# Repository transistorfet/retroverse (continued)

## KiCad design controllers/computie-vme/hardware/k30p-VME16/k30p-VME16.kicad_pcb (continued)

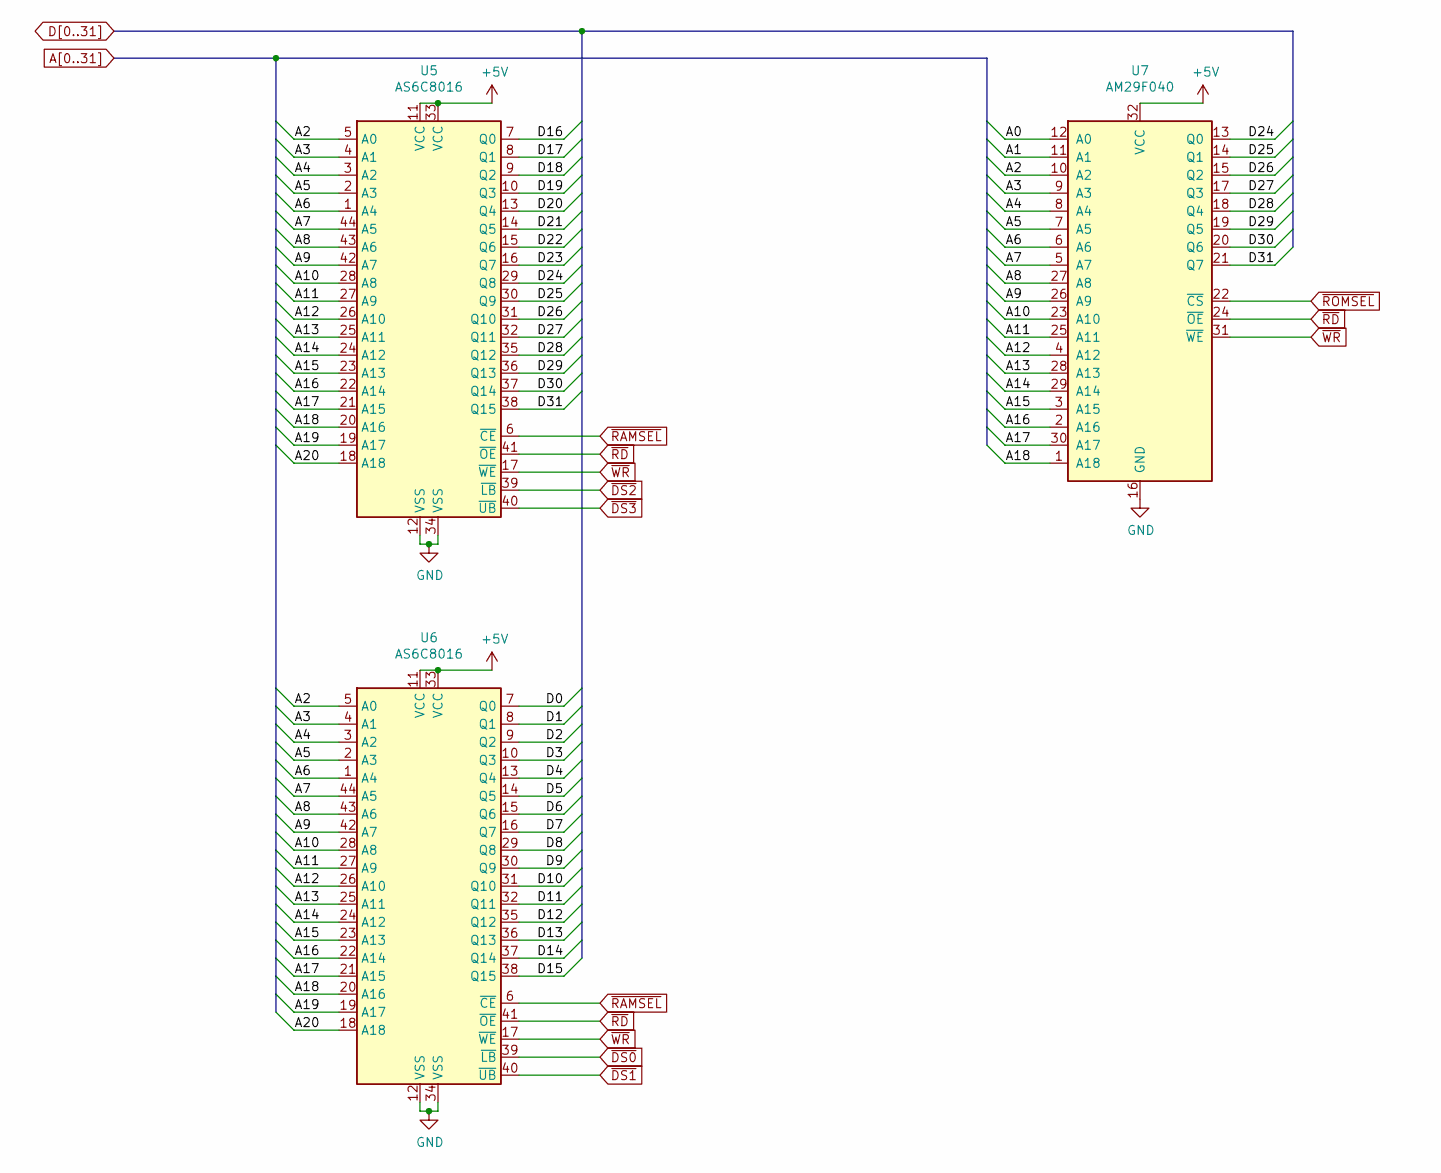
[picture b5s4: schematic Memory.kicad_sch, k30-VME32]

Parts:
U5, U6: AS6C8016; TSOP-II-44_10.16x18.41mm_P0.8mm
U7: AM29F040; PLCC-32_THT-Socket

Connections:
+5V: U5.11 (VCC), U5.33 (VCC), U6.11 (VCC), U6.33 (VCC), U7.32 (VCC); also elsewhere on the board
A0: U7.12 (A0)
A1: U7.11 (A1); also elsewhere on the board
A2: U5.5 (A0), U6.5 (A0), U7.10 (A2); also elsewhere on the board
A3: U5.4 (A1), U6.4 (A1), U7.9 (A3); also elsewhere on the board
A4: U5.3 (A2), U6.3 (A2), U7.8 (A4); also elsewhere on the board
A5: U5.2 (A3), U6.2 (A3), U7.7 (A5)
A6: U5.1 (A4), U6.1 (A4), U7.6 (A6)
A7: U5.44 (A5), U6.44 (A5), U7.5 (A7)
A8: U5.43 (A6), U6.43 (A6), U7.27 (A8)
A9: U5.42 (A7), U6.42 (A7), U7.26 (A9)
A10: U5.28 (A8), U6.28 (A8), U7.23 (A10)
A11: U5.27 (A9), U6.27 (A9), U7.25 (A11)
A12: U5.26 (A10), U6.26 (A10), U7.4 (A12)
A13: U5.25 (A11), U6.25 (A11), U7.28 (A13)
A14: U5.24 (A12), U6.24 (A12), U7.29 (A14)
A15: U5.23 (A13), U6.23 (A13), U7.3 (A15)
A16: U5.22 (A14), U6.22 (A14), U7.2 (A16)
A17: U5.21 (A15), U6.21 (A15), U7.30 (A17)
A18: U5.20 (A16), U6.20 (A16), U7.1 (A18)
A19: U5.19 (A17), U6.19 (A17)
A20: U5.18 (A18), U6.18 (A18)
D0: U6.7 (Q0)
D1: U6.8 (Q1)
D2: U6.9 (Q2)
D3: U6.10 (Q3)
D4: U6.13 (Q4)
D5: U6.14 (Q5)
D6: U6.15 (Q6)
D7: U6.16 (Q7)
D8: U6.29 (Q8)
D9: U6.30 (Q9)
D10: U6.31 (Q10)
D11: U6.32 (Q11)
D12: U6.35 (Q12)
D13: U6.36 (Q13)
D14: U6.37 (Q14)
D15: U6.38 (Q15)
D16: U5.7 (Q0)
D17: U5.8 (Q1)
D18: U5.9 (Q2)
D19: U5.10 (Q3)
D20: U5.13 (Q4)
D21: U5.14 (Q5)
D22: U5.15 (Q6)
D23: U5.16 (Q7)
D24: U5.29 (Q8), U7.13 (Q0); also elsewhere on the board
D25: U5.30 (Q9), U7.14 (Q1); also elsewhere on the board
D26: U5.31 (Q10), U7.15 (Q2); also elsewhere on the board
D27: U5.32 (Q11), U7.17 (Q3); also elsewhere on the board
D28: U5.35 (Q12), U7.18 (Q4); also elsewhere on the board
D29: U5.36 (Q13), U7.19 (Q5); also elsewhere on the board
D30: U5.37 (Q14), U7.20 (Q6); also elsewhere on the board
D31: U5.38 (Q15), U7.21 (Q7); also elsewhere on the board
GND: U5.12 (VSS), U5.34 (VSS), U6.12 (VSS), U6.34 (VSS), U7.16 (GND); also elsewhere on the board
~DS0: U6.39 (~LB)
~DS1: U6.40 (~UB)
~DS2: U5.39 (~LB)
~DS3: U5.40 (~UB)
~RAMSEL: U5.6 (~CE), U6.6 (~CE)
~RD: U5.41 (~OE), U6.41 (~OE), U7.24 (~OE); also elsewhere on the board
~ROMSEL: U7.22 (~CS)
~WR: U5.17 (~WE), U6.17 (~WE), U7.31 (~WE); also elsewhere on the board

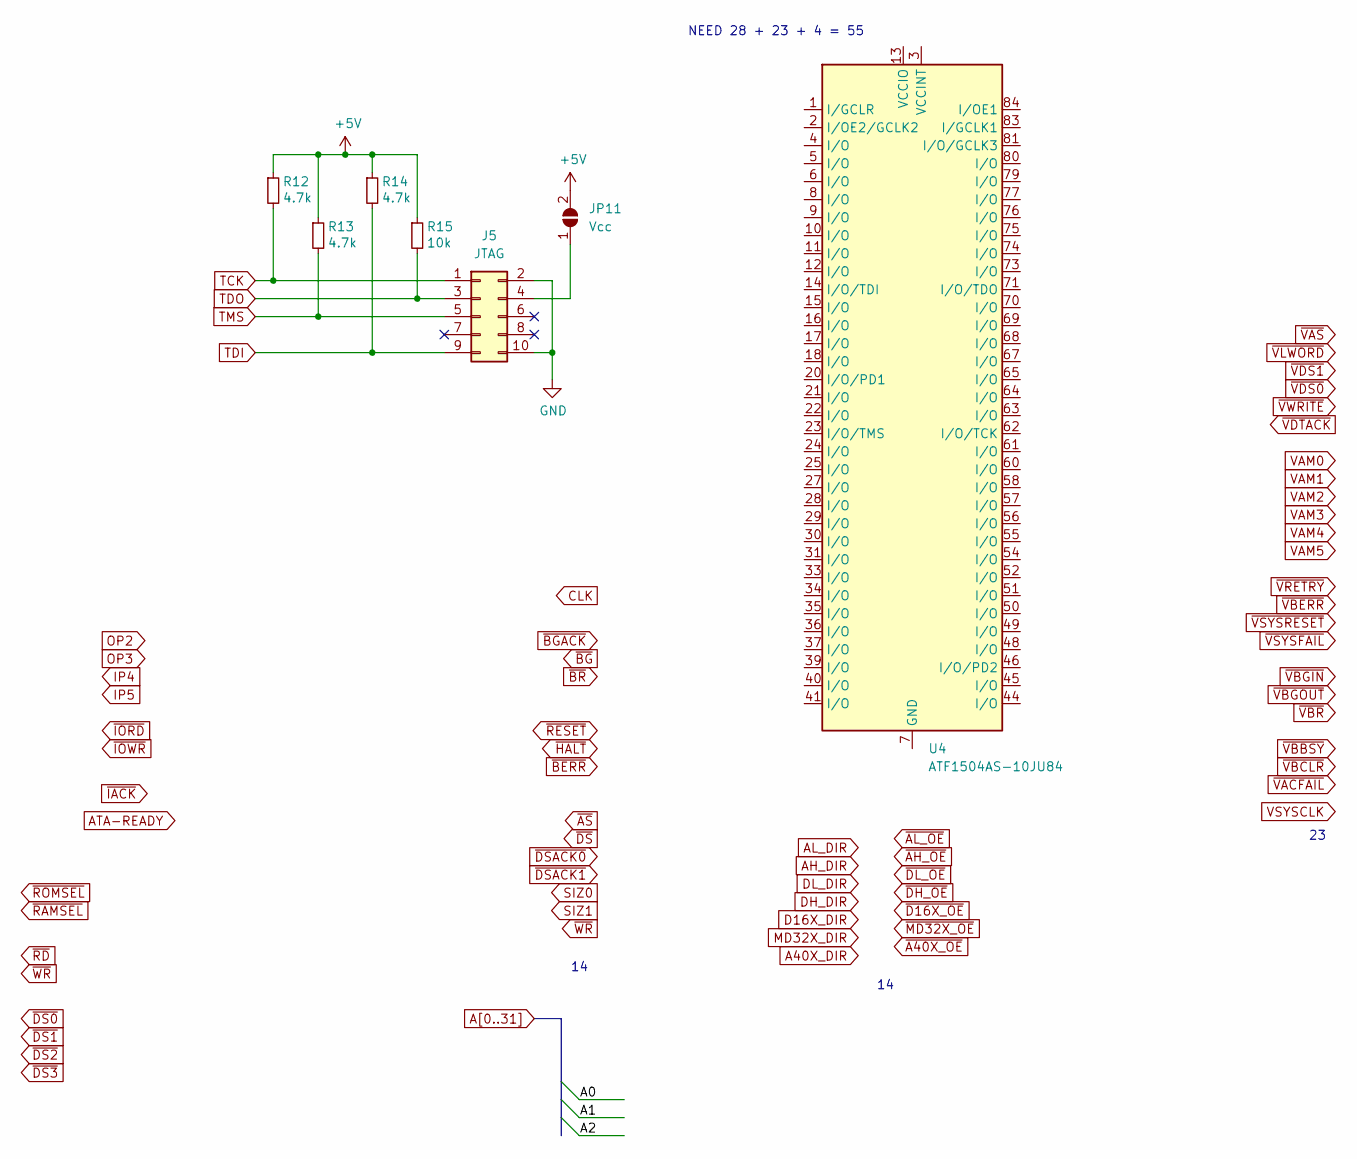
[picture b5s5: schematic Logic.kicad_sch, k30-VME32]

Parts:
J5: JTAG; PinHeader_2x05_P2.54mm_Vertical
JP11: Vcc; SolderJumper-2_P1.3mm_Open_RoundedPad1.0x1.5mm
R12, R13, R14: 4.7k; R_Axial_DIN0204_L3.6mm_D1.6mm_P5.08mm_Horizontal
R15: 10k; R_Axial_DIN0204_L3.6mm_D1.6mm_P5.08mm_Horizontal
U4: ATF1504AS-10JU84; PLCC-84_THT-Socket

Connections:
+5V: JP11.2 (B), R12.1, R13.1, R14.1, R15.1; also elsewhere on the board
GND: J5.2, J5.10; also elsewhere on the board
unnamed: J5.4, JP11.1 (A)
unnamed: U4.7 (GND), U4.19 (GND), U4.32 (GND), U4.42 (GND), U4.47 (GND), U4.59 (GND), U4.72 (GND), U4.82 (GND)
unnamed: U4.3 (VCCINT), U4.43 (VCCINT)
unnamed: U4.13 (VCCIO), U4.26 (VCCIO), U4.38 (VCCIO), U4.53 (VCCIO), U4.66 (VCCIO), U4.78 (VCCIO)
TCK: J5.1, R12.2
TDI: J5.9, R14.2
TDO: J5.3, R15.2
TMS: J5.5, R13.2

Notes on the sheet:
NEED 28 + 23 + 4 = 55

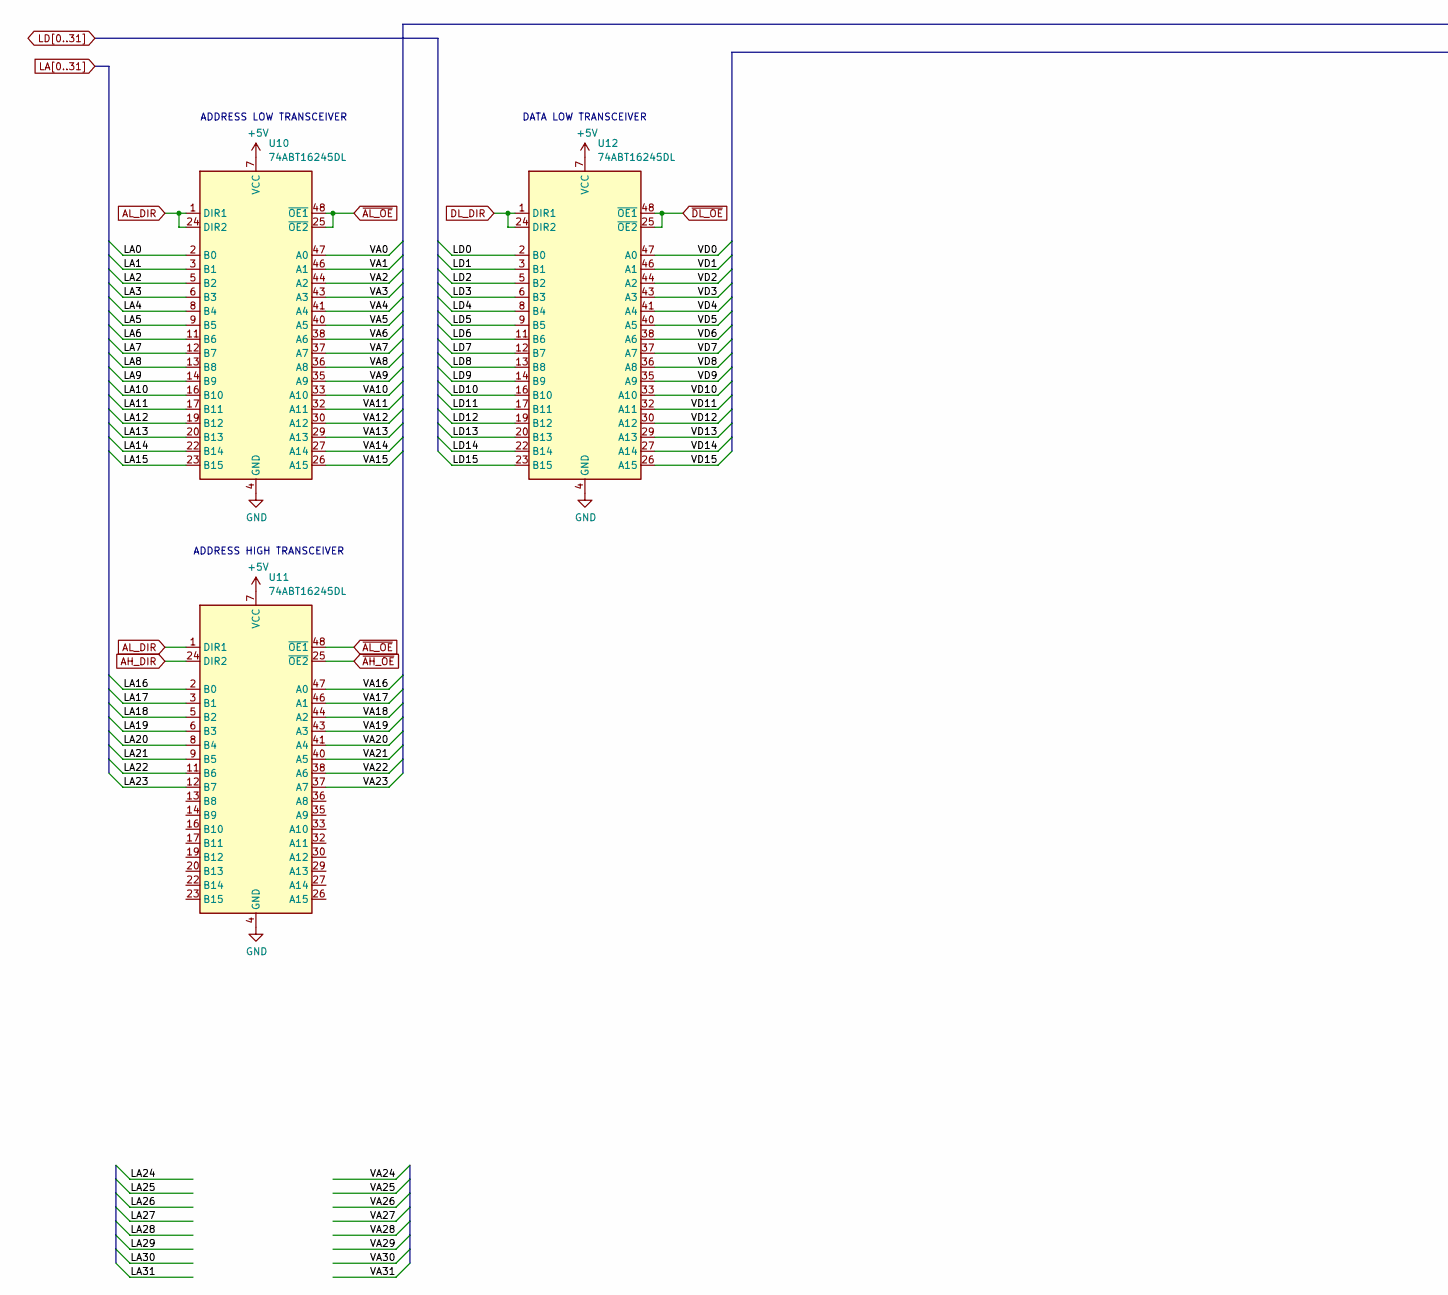
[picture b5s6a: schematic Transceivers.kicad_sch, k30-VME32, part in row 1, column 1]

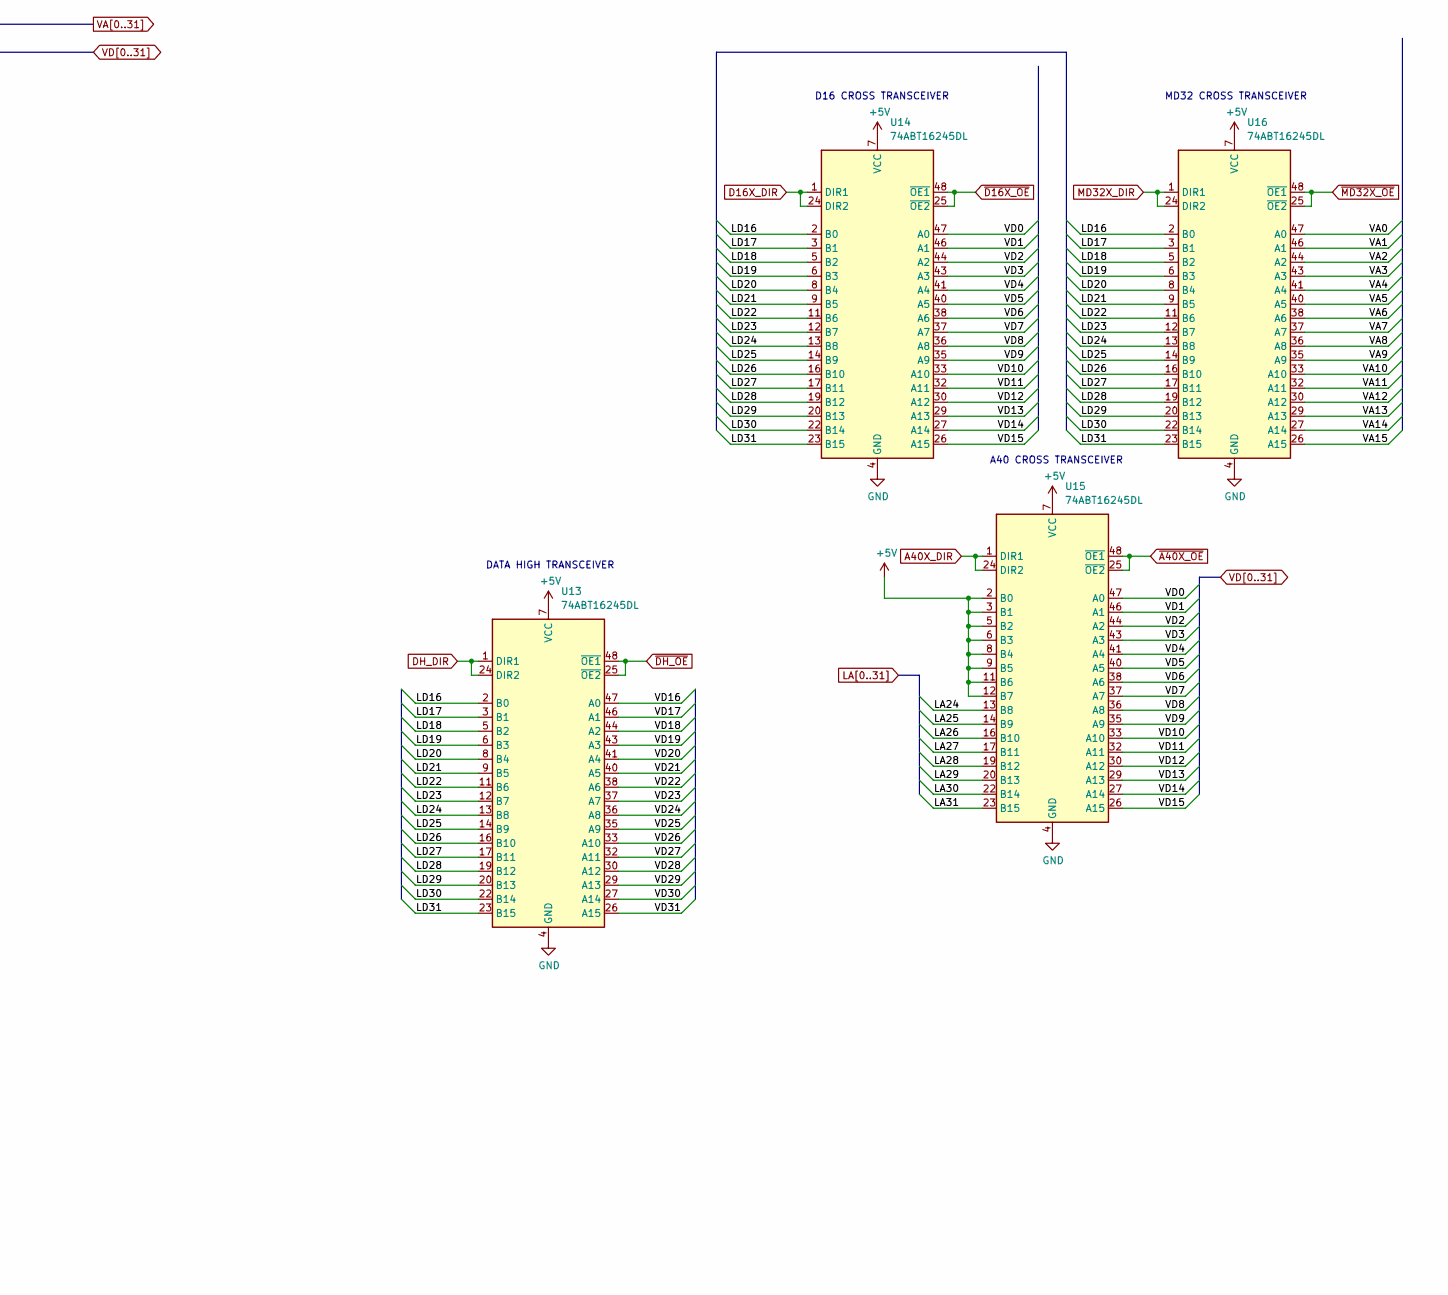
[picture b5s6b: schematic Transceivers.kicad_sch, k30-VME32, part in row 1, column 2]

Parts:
U10, U11, U12, U13, U14, U15, U16: 74ABT16245DL; TSSOP-48_6.1x12.5mm_P0.5mm

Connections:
+5V: U10.7 (VCC), U10.18 (VCC), U10.31 (VCC), U10.42 (VCC), U11.7 (VCC), U11.18 (VCC), U11.31 (VCC), U11.42 (VCC), U12.7 (VCC), U12.18 (VCC), U12.31 (VCC), U12.42 (VCC), U13.7 (VCC), U13.18 (VCC), U13.31 (VCC), U13.42 (VCC), U14.7 (VCC), U14.18 (VCC), U14.31 (VCC), U14.42 (VCC), U15.2 (B0), U15.3 (B1), U15.5 (B2), U15.6 (B3), U15.7 (VCC), U15.8 (B4), U15.9 (B5), U15.11 (B6), U15.12 (B7), U15.18 (VCC), U15.31 (VCC), U15.42 (VCC), U16.7 (VCC), U16.18 (VCC), U16.31 (VCC), U16.42 (VCC); also elsewhere on the board
A40X_DIR: U15.1 (DIR1), U15.24 (DIR2)
AH_DIR: U11.24 (DIR2)
AL_DIR: U10.1 (DIR1), U10.24 (DIR2), U11.1 (DIR1)
D16X_DIR: U14.1 (DIR1), U14.24 (DIR2)
DH_DIR: U13.1 (DIR1), U13.24 (DIR2)
DL_DIR: U12.1 (DIR1), U12.24 (DIR2)
GND: U10.4 (GND), U10.10 (GND), U10.15 (GND), U10.21 (GND), U10.28 (GND), U10.34 (GND), U10.39 (GND), U10.45 (GND), U11.4 (GND), U11.10 (GND), U11.15 (GND), U11.21 (GND), U11.28 (GND), U11.34 (GND), U11.39 (GND), U11.45 (GND), U12.4 (GND), U12.10 (GND), U12.15 (GND), U12.21 (GND), U12.28 (GND), U12.34 (GND), U12.39 (GND), U12.45 (GND), U13.4 (GND), U13.10 (GND), U13.15 (GND), U13.21 (GND), U13.28 (GND), U13.34 (GND), U13.39 (GND), U13.45 (GND), U14.4 (GND), U14.10 (GND), U14.15 (GND), U14.21 (GND), U14.28 (GND), U14.34 (GND), U14.39 (GND), U14.45 (GND), U15.4 (GND), U15.10 (GND), U15.15 (GND), U15.21 (GND), U15.28 (GND), U15.34 (GND), U15.39 (GND), U15.45 (GND), U16.4 (GND), U16.10 (GND), U16.15 (GND), U16.21 (GND), U16.28 (GND), U16.34 (GND), U16.39 (GND), U16.45 (GND); also elsewhere on the board
LA0: U10.2 (B0); also elsewhere on the board
LA1: U10.3 (B1); also elsewhere on the board
LA2: U10.5 (B2); also elsewhere on the board
LA3: U10.6 (B3); also elsewhere on the board
LA4: U10.8 (B4); also elsewhere on the board
LA5: U10.9 (B5); also elsewhere on the board
LA6: U10.11 (B6); also elsewhere on the board
LA7: U10.12 (B7); also elsewhere on the board
LA8: U10.13 (B8); also elsewhere on the board
LA9: U10.14 (B9); also elsewhere on the board
LA10: U10.16 (B10); also elsewhere on the board
LA11: U10.17 (B11); also elsewhere on the board
LA12: U10.19 (B12); also elsewhere on the board
LA13: U10.20 (B13); also elsewhere on the board
LA14: U10.22 (B14); also elsewhere on the board
LA15: U10.23 (B15); also elsewhere on the board
LA16: U11.2 (B0); also elsewhere on the board
LA17: U11.3 (B1); also elsewhere on the board
LA18: U11.5 (B2); also elsewhere on the board
LA19: U11.6 (B3); also elsewhere on the board
LA20: U11.8 (B4); also elsewhere on the board
LA21: U11.9 (B5); also elsewhere on the board
LA22: U11.11 (B6); also elsewhere on the board
LA23: U11.12 (B7); also elsewhere on the board
LA24: U15.13 (B8); also elsewhere on the board
LA25: U15.14 (B9); also elsewhere on the board
LA26: U15.16 (B10); also elsewhere on the board
LA27: U15.17 (B11); also elsewhere on the board
LA28: U15.19 (B12); also elsewhere on the board
LA29: U15.20 (B13); also elsewhere on the board
LA30: U15.22 (B14); also elsewhere on the board
LA31: U15.23 (B15); also elsewhere on the board
LD0: U12.2 (B0); also elsewhere on the board
LD1: U12.3 (B1); also elsewhere on the board
LD2: U12.5 (B2); also elsewhere on the board
LD3: U12.6 (B3); also elsewhere on the board
LD4: U12.8 (B4); also elsewhere on the board
LD5: U12.9 (B5); also elsewhere on the board
LD6: U12.11 (B6); also elsewhere on the board
LD7: U12.12 (B7); also elsewhere on the board
LD8: U12.13 (B8); also elsewhere on the board
LD9: U12.14 (B9); also elsewhere on the board
LD10: U12.16 (B10); also elsewhere on the board
LD11: U12.17 (B11); also elsewhere on the board
LD12: U12.19 (B12); also elsewhere on the board
LD13: U12.20 (B13); also elsewhere on the board
LD14: U12.22 (B14); also elsewhere on the board
LD15: U12.23 (B15); also elsewhere on the board
LD16: U13.2 (B0), U14.2 (B0), U16.2 (B0); also elsewhere on the board
LD17: U13.3 (B1), U14.3 (B1), U16.3 (B1); also elsewhere on the board
LD18: U13.5 (B2), U14.5 (B2), U16.5 (B2); also elsewhere on the board
LD19: U13.6 (B3), U14.6 (B3), U16.6 (B3); also elsewhere on the board
LD20: U13.8 (B4), U14.8 (B4), U16.8 (B4); also elsewhere on the board
LD21: U13.9 (B5), U14.9 (B5), U16.9 (B5); also elsewhere on the board
LD22: U13.11 (B6), U14.11 (B6), U16.11 (B6); also elsewhere on the board
LD23: U13.12 (B7), U14.12 (B7), U16.12 (B7); also elsewhere on the board
LD24: U13.13 (B8), U14.13 (B8), U16.13 (B8); also elsewhere on the board
LD25: U13.14 (B9), U14.14 (B9), U16.14 (B9); also elsewhere on the board
LD26: U13.16 (B10), U14.16 (B10), U16.16 (B10); also elsewhere on the board
LD27: U13.17 (B11), U14.17 (B11), U16.17 (B11); also elsewhere on the board
LD28: U13.19 (B12), U14.19 (B12), U16.19 (B12); also elsewhere on the board
LD29: U13.20 (B13), U14.20 (B13), U16.20 (B13); also elsewhere on the board
LD30: U13.22 (B14), U14.22 (B14), U16.22 (B14); also elsewhere on the board
LD31: U13.23 (B15), U14.23 (B15), U16.23 (B15); also elsewhere on the board
MD32X_DIR: U16.1 (DIR1), U16.24 (DIR2)
VA0: U10.47 (A0), U16.47 (A0)
VA1: U10.46 (A1), U16.46 (A1); also elsewhere on the board
VA2: U10.44 (A2), U16.44 (A2); also elsewhere on the board
VA3: U10.43 (A3), U16.43 (A3); also elsewhere on the board
VA4: U10.41 (A4), U16.41 (A4); also elsewhere on the board
VA5: U10.40 (A5), U16.40 (A5); also elsewhere on the board
VA6: U10.38 (A6), U16.38 (A6); also elsewhere on the board
VA7: U10.37 (A7), U16.37 (A7); also elsewhere on the board
VA8: U10.36 (A8), U16.36 (A8); also elsewhere on the board
VA9: U10.35 (A9), U16.35 (A9); also elsewhere on the board
VA10: U10.33 (A10), U16.33 (A10); also elsewhere on the board
VA11: U10.32 (A11), U16.32 (A11); also elsewhere on the board
VA12: U10.30 (A12), U16.30 (A12); also elsewhere on the board
VA13: U10.29 (A13), U16.29 (A13); also elsewhere on the board
VA14: U10.27 (A14), U16.27 (A14); also elsewhere on the board
VA15: U10.26 (A15), U16.26 (A15); also elsewhere on the board
VA16: U11.47 (A0); also elsewhere on the board
VA17: U11.46 (A1); also elsewhere on the board
VA18: U11.44 (A2); also elsewhere on the board
VA19: U11.43 (A3); also elsewhere on the board
VA20: U11.41 (A4); also elsewhere on the board
VA21: U11.40 (A5); also elsewhere on the board
VA22: U11.38 (A6); also elsewhere on the board
VA23: U11.37 (A7); also elsewhere on the board
VD0: U12.47 (A0), U14.47 (A0), U15.47 (A0); also elsewhere on the board
VD1: U12.46 (A1), U14.46 (A1), U15.46 (A1); also elsewhere on the board
VD2: U12.44 (A2), U14.44 (A2), U15.44 (A2); also elsewhere on the board
VD3: U12.43 (A3), U14.43 (A3), U15.43 (A3); also elsewhere on the board
VD4: U12.41 (A4), U14.41 (A4), U15.41 (A4); also elsewhere on the board
VD5: U12.40 (A5), U14.40 (A5), U15.40 (A5); also elsewhere on the board
VD6: U12.38 (A6), U14.38 (A6), U15.38 (A6); also elsewhere on the board
VD7: U12.37 (A7), U14.37 (A7), U15.37 (A7); also elsewhere on the board
VD8: U12.36 (A8), U14.36 (A8), U15.36 (A8); also elsewhere on the board
VD9: U12.35 (A9), U14.35 (A9), U15.35 (A9); also elsewhere on the board
VD10: U12.33 (A10), U14.33 (A10), U15.33 (A10); also elsewhere on the board
VD11: U12.32 (A11), U14.32 (A11), U15.32 (A11); also elsewhere on the board
VD12: U12.30 (A12), U14.30 (A12), U15.30 (A12); also elsewhere on the board
VD13: U12.29 (A13), U14.29 (A13), U15.29 (A13); also elsewhere on the board
VD14: U12.27 (A14), U14.27 (A14), U15.27 (A14); also elsewhere on the board
VD15: U12.26 (A15), U14.26 (A15), U15.26 (A15); also elsewhere on the board
VD16: U13.47 (A0)
VD17: U13.46 (A1)
VD18: U13.44 (A2)
VD19: U13.43 (A3)
VD20: U13.41 (A4)
VD21: U13.40 (A5)
VD22: U13.38 (A6)
VD23: U13.37 (A7)
VD24: U13.36 (A8)
VD25: U13.35 (A9)
VD26: U13.33 (A10)
VD27: U13.32 (A11)
VD28: U13.30 (A12)
VD29: U13.29 (A13)
VD30: U13.27 (A14)
VD31: U13.26 (A15)
~A40X_OE: U15.25 (~OE2), U15.48 (~OE1)
~AH_OE: U11.25 (~OE2)
~AL_OE: U10.25 (~OE2), U10.48 (~OE1), U11.48 (~OE1)
~D16X_OE: U14.25 (~OE2), U14.48 (~OE1)
~DH_OE: U13.25 (~OE2), U13.48 (~OE1)
~DL_OE: U12.25 (~OE2), U12.48 (~OE1)
~MD32X_OE: U16.25 (~OE2), U16.48 (~OE1)

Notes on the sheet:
D16 CROSS TRANSCEIVER
ADDRESS HIGH TRANSCEIVER
MD32 CROSS TRANSCEIVER
ADDRESS LOW TRANSCEIVER
A40 CROSS TRANSCEIVER
DATA LOW TRANSCEIVER
DATA HIGH TRANSCEIVER

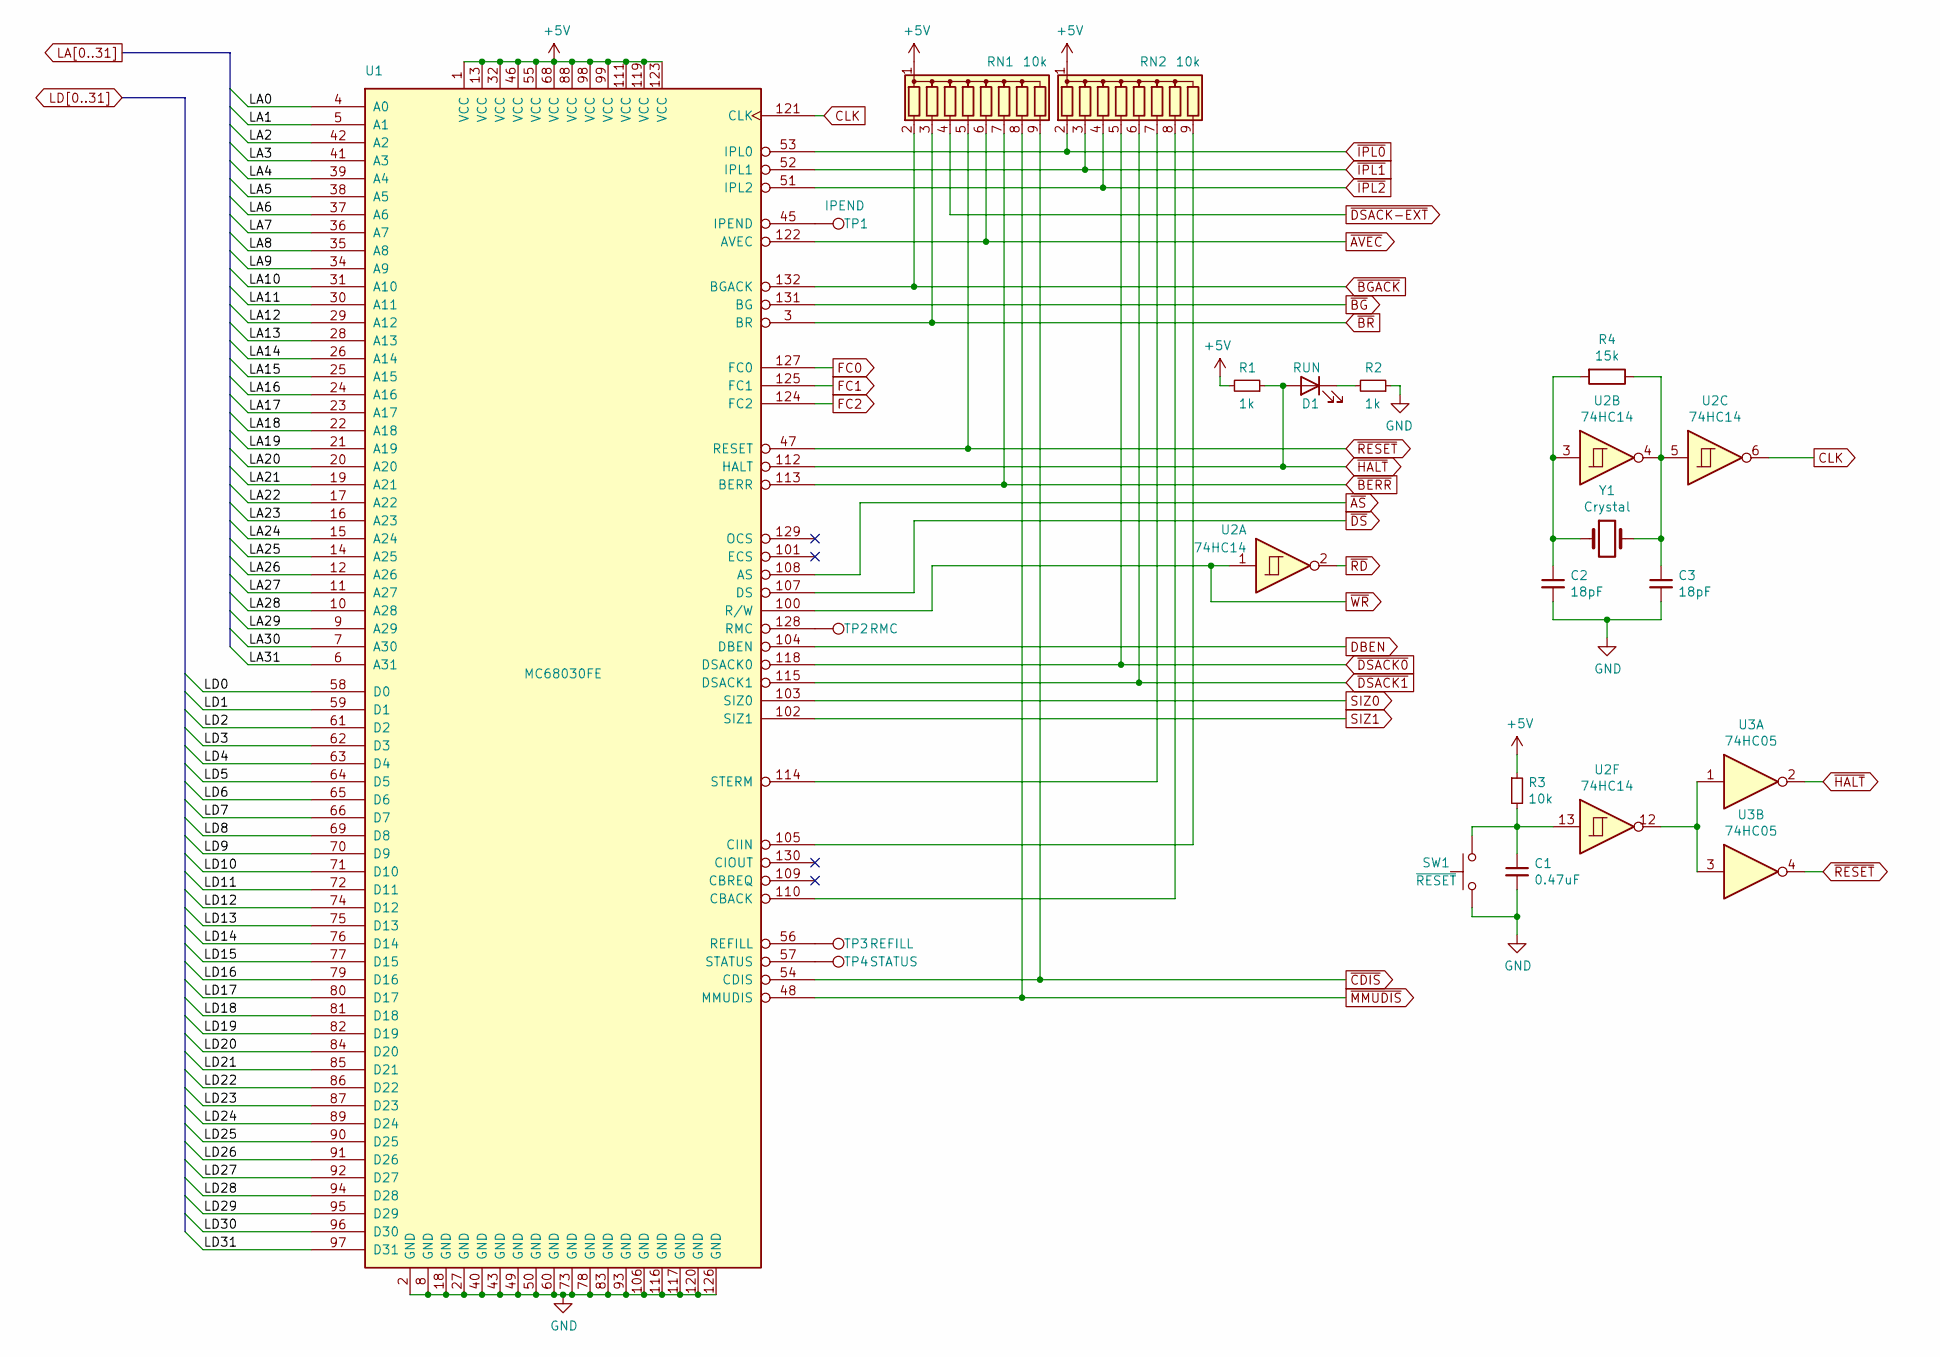
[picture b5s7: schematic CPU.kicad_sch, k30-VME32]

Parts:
C1: 0.47uF; C_Disc_D3.0mm_W2.0mm_P2.50mm
C2, C3: 18pF; C_Disc_D3.0mm_W2.0mm_P2.50mm
D1: RUN; LED_D5.0mm
R1, R2: 1k; R_Axial_DIN0204_L3.6mm_D1.6mm_P5.08mm_Horizontal
R3: 10k; R_Axial_DIN0204_L3.6mm_D1.6mm_P5.08mm_Horizontal
R4: 15k; R_Axial_DIN0204_L3.6mm_D1.6mm_P5.08mm_Horizontal
RN1, RN2: 10k; R_Array_SIP9
SW1: ~{RESET}; SW_PUSH_6mm
TP1: IPEND; TestPoint_THTPad_2.0x2.0mm_Drill1.0mm
TP2: RMC; TestPoint_THTPad_2.0x2.0mm_Drill1.0mm
TP3: REFILL; TestPoint_THTPad_2.0x2.0mm_Drill1.0mm
TP4: STATUS; TestPoint_THTPad_2.0x2.0mm_Drill1.0mm
U1: MC68030FE; PQFP-132_24x24mm_P0.635mm
U2: 74HC14; TSSOP-14_4.4x5mm_P0.65mm
U3: 74HC05; TSSOP-14_4.4x5mm_P0.65mm
Y1: Crystal; Crystal_HC49-4H_Vertical

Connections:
+5V: R1.2, R3.1, RN1.1 (common), RN2.1 (common), U1.1 (VCC), U1.13 (VCC), U1.32 (VCC), U1.46 (VCC), U1.55 (VCC), U1.68 (VCC), U1.88 (VCC), U1.98 (VCC), U1.99 (VCC), U1.111 (VCC), U1.119 (VCC), U1.123 (VCC); also elsewhere on the board
CLK: U1.121 (CLK), U2.6
DBEN: U1.104 (DBEN)
FC0: U1.127 (FC0)
FC1: U1.125 (FC1)
FC2: U1.124 (FC2)
GND: C1.2, C2.2, C3.2, R2.1, SW1.1, U1.2 (GND), U1.8 (GND), U1.18 (GND), U1.27 (GND), U1.40 (GND), U1.43 (GND), U1.49 (GND), U1.50 (GND), U1.60 (GND), U1.73 (GND), U1.78 (GND), U1.83 (GND), U1.93 (GND), U1.106 (GND), U1.116 (GND), U1.117 (GND), U1.120 (GND), U1.126 (GND); also elsewhere on the board
LA0: U1.4 (A0); also elsewhere on the board
LA1: U1.5 (A1); also elsewhere on the board
LA2: U1.42 (A2); also elsewhere on the board
LA3: U1.41 (A3); also elsewhere on the board
LA4: U1.39 (A4); also elsewhere on the board
LA5: U1.38 (A5); also elsewhere on the board
LA6: U1.37 (A6); also elsewhere on the board
LA7: U1.36 (A7); also elsewhere on the board
LA8: U1.35 (A8); also elsewhere on the board
LA9: U1.34 (A9); also elsewhere on the board
LA10: U1.31 (A10); also elsewhere on the board
LA11: U1.30 (A11); also elsewhere on the board
LA12: U1.29 (A12); also elsewhere on the board
LA13: U1.28 (A13); also elsewhere on the board
LA14: U1.26 (A14); also elsewhere on the board
LA15: U1.25 (A15); also elsewhere on the board
LA16: U1.24 (A16); also elsewhere on the board
LA17: U1.23 (A17); also elsewhere on the board
LA18: U1.22 (A18); also elsewhere on the board
LA19: U1.21 (A19); also elsewhere on the board
LA20: U1.20 (A20); also elsewhere on the board
LA21: U1.19 (A21); also elsewhere on the board
LA22: U1.17 (A22); also elsewhere on the board
LA23: U1.16 (A23); also elsewhere on the board
LA24: U1.15 (A24); also elsewhere on the board
LA25: U1.14 (A25); also elsewhere on the board
LA26: U1.12 (A26); also elsewhere on the board
LA27: U1.11 (A27); also elsewhere on the board
LA28: U1.10 (A28); also elsewhere on the board
LA29: U1.9 (A29); also elsewhere on the board
LA30: U1.7 (A30); also elsewhere on the board
LA31: U1.6 (A31); also elsewhere on the board
LD0: U1.58 (D0); also elsewhere on the board
LD1: U1.59 (D1); also elsewhere on the board
LD2: U1.61 (D2); also elsewhere on the board
LD3: U1.62 (D3); also elsewhere on the board
LD4: U1.63 (D4); also elsewhere on the board
LD5: U1.64 (D5); also elsewhere on the board
LD6: U1.65 (D6); also elsewhere on the board
LD7: U1.66 (D7); also elsewhere on the board
LD8: U1.69 (D8); also elsewhere on the board
LD9: U1.70 (D9); also elsewhere on the board
LD10: U1.71 (D10); also elsewhere on the board
LD11: U1.72 (D11); also elsewhere on the board
LD12: U1.74 (D12); also elsewhere on the board
LD13: U1.75 (D13); also elsewhere on the board
LD14: U1.76 (D14); also elsewhere on the board
LD15: U1.77 (D15); also elsewhere on the board
LD16: U1.79 (D16); also elsewhere on the board
LD17: U1.80 (D17); also elsewhere on the board
LD18: U1.81 (D18); also elsewhere on the board
LD19: U1.82 (D19); also elsewhere on the board
LD20: U1.84 (D20); also elsewhere on the board
LD21: U1.85 (D21); also elsewhere on the board
LD22: U1.86 (D22); also elsewhere on the board
LD23: U1.87 (D23); also elsewhere on the board
LD24: U1.89 (D24); also elsewhere on the board
LD25: U1.90 (D25); also elsewhere on the board
LD26: U1.91 (D26); also elsewhere on the board
LD27: U1.92 (D27); also elsewhere on the board
LD28: U1.94 (D28); also elsewhere on the board
LD29: U1.95 (D29); also elsewhere on the board
LD30: U1.96 (D30); also elsewhere on the board
LD31: U1.97 (D31); also elsewhere on the board
unnamed: C1.1, R3.2, SW1.2, U2.13
unnamed: C2.1, R4.2, U2.3, Y1.1
unnamed: C3.1, R4.1, U2.4, U2.5, Y1.2
unnamed: D1.1 (K), R2.2
unnamed: RN2.7 (R6), U1.114 (STERM)
unnamed: RN2.8 (R7), U1.110 (CBACK)
unnamed: RN2.9 (R8), U1.105 (CIIN)
unnamed: TP1.1, U1.45 (IPEND)
unnamed: TP3.1, U1.56 (REFILL)
unnamed: TP2.1, U1.128 (RMC)
unnamed: TP4.1, U1.57 (STATUS)
unnamed: U2.12, U3.1, U3.3
SIZ0: U1.103 (SIZ0)
SIZ1: U1.102 (SIZ1)
~AS: U1.108 (AS)
~AVEC: RN1.6 (R5), U1.122 (AVEC)
~BERR: RN1.7 (R6), U1.113 (BERR)
~BGACK: RN1.2 (R1), U1.132 (BGACK)
~BG: U1.131 (BG)
~BR: RN1.3 (R2), U1.3 (BR)
~CDIS: RN1.9 (R8), U1.54 (CDIS)
~DSACK0: RN2.5 (R4), U1.118 (DSACK0); also elsewhere on the board
~DSACK1: RN2.6 (R5), U1.115 (DSACK1)
~DSACK-EXT: RN1.4 (R3)
~DS: U1.107 (DS)
~HALT: D1.2 (A), R1.1, U1.112 (HALT), U3.2
~IPL0: RN2.2 (R1), U1.53 (IPL0)
~IPL1: RN2.3 (R2), U1.52 (IPL1); also elsewhere on the board
~IPL2: RN2.4 (R3), U1.51 (IPL2)
~MMUDIS: RN1.8 (R7), U1.48 (MMUDIS)
~RD: U2.2; also elsewhere on the board
~RESET: RN1.5 (R4), U1.47 (RESET), U3.4; also elsewhere on the board
~WR: U1.100 (R/W), U2.1; also elsewhere on the board

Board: 2 copper layers, 69 parts (0 on the bottom side), 208 nets, no tracks yet.
